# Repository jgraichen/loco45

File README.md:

Servo 3-pin to RJ45 Adapter

An adapter board to pass up to 8 servo decoders signals to 4 RJ45 connectors.

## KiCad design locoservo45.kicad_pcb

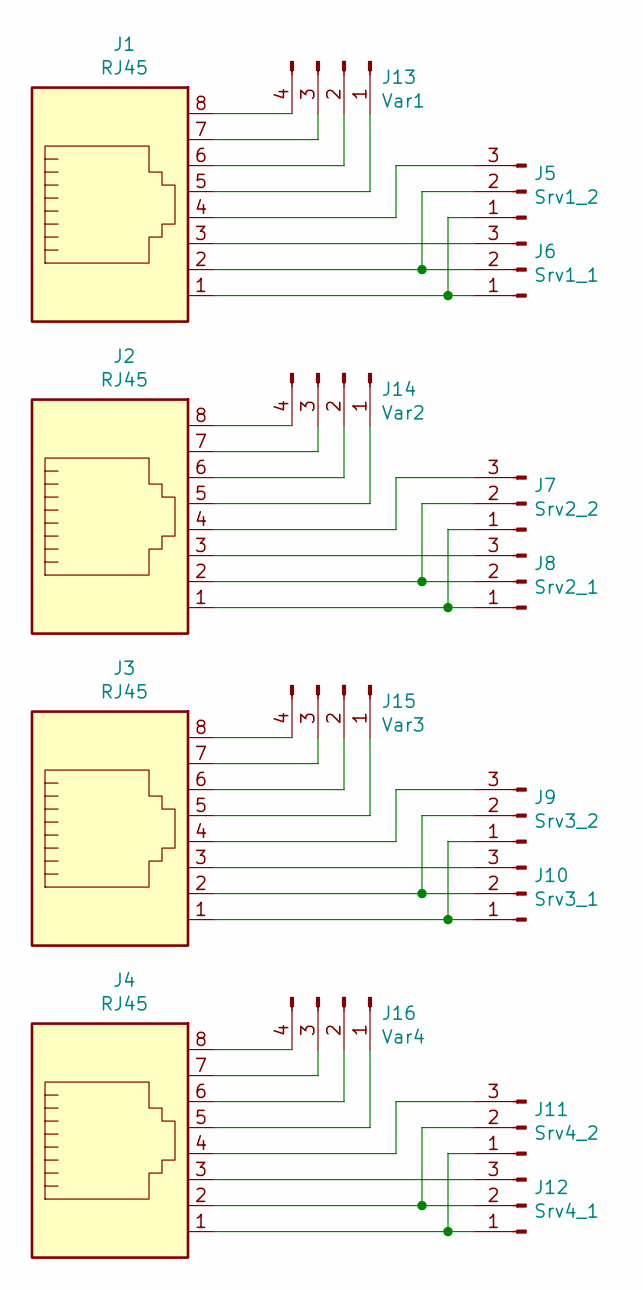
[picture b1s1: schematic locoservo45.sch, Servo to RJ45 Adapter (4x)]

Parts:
J1, J2, J3, J4: RJ45; RJ45_Amphenol_54602-x08_Horizontal
J5: Srv1_2; PinHeader_1x03_P2.54mm_Horizontal
J6: Srv1_1; PinHeader_1x03_P2.54mm_Horizontal
J7: Srv2_2; PinHeader_1x03_P2.54mm_Horizontal
J8: Srv2_1; PinHeader_1x03_P2.54mm_Horizontal
J9: Srv3_2; PinHeader_1x03_P2.54mm_Horizontal
J10: Srv3_1; PinHeader_1x03_P2.54mm_Horizontal
J11: Srv4_2; PinHeader_1x03_P2.54mm_Horizontal
J12: Srv4_1; PinHeader_1x03_P2.54mm_Horizontal
J13: Var1; PinHeader_1x04_P2.54mm_Horizontal
J14: Var2; PinHeader_1x04_P2.54mm_Horizontal
J15: Var3; PinHeader_1x04_P2.54mm_Horizontal
J16: Var4; PinHeader_1x04_P2.54mm_Horizontal

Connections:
unnamed: J1.1, J5.1, J6.1
unnamed: J1.2, J5.2, J6.2
unnamed: J1.3, J6.3
unnamed: J1.4, J5.3
unnamed: J1.5, J13.1
unnamed: J1.6, J13.2
unnamed: J1.7, J13.3
unnamed: J1.8, J13.4
unnamed: J2.1, J7.1, J8.1
unnamed: J2.2, J7.2, J8.2
unnamed: J2.3, J8.3
unnamed: J2.4, J7.3
unnamed: J3.4, J9.3
unnamed: J3.1, J9.1, J10.1
unnamed: J3.2, J9.2, J10.2
unnamed: J3.3, J10.3
unnamed: J4.1, J11.1, J12.1
unnamed: J4.2, J11.2, J12.2
unnamed: J4.4, J11.3
unnamed: J4.3, J12.3
unnamed: J2.5, J14.1
unnamed: J2.6, J14.2
unnamed: J2.7, J14.3
unnamed: J2.8, J14.4
unnamed: J3.5, J15.1
unnamed: J3.6, J15.2
unnamed: J3.7, J15.3
unnamed: J3.8, J15.4
unnamed: J4.5, J16.1
unnamed: J4.6, J16.2
unnamed: J4.7, J16.3
unnamed: J4.8, J16.4

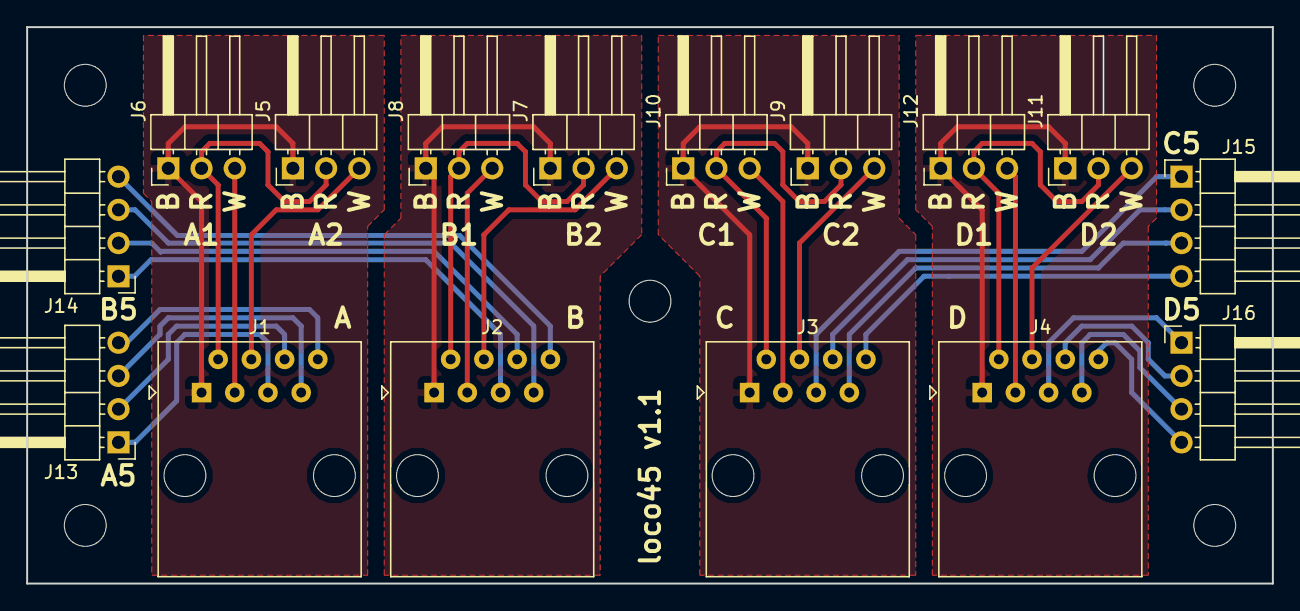
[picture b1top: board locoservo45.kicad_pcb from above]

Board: 2 copper layers, 95.2 x 42.5 mm, 16 parts (0 on the bottom side), 32 nets.

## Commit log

2019-03-24 v1.0
2019-03-24 Add edge cuts; Fix mounting holes
2019-03-24 Add masking for over-the-edge silkscreen
2019-03-24 added ground planes, re-routed connections
2019-12-15 Add readme
    Fix #2
2019-12-15 v1.1
